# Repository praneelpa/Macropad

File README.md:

# Custom 6-Key Macropad for macOS

A compact 6-key macropad designed for macOS users, optimized for students. Features tap/hold combos for frequently used shortcuts like screenshots, clipboard, app switching, undo/redo, sleep, and quit.

---

## Images

### Overall Macropad
The overall part has a top case and a bottom case that fit together using screws (US 6# Screw).
It contains a PCB with the required components that sits on the bottom base, and the CherryMX keys stick out from the top base for access.

Made using Autodesk Fusion!

### Schematic
Made in KiCad!

### PCB
Made in KiCad!
Used the Cherry_MX_1.00u_PCB footprint from KiCad

---

## BOM (Bill of Materials)
Everything needed to make the macropad.
| Quantity | Part Description                | Notes |
|----------|--------------------------------|-------|
| 1        | XIAO RP2040 DIP                 | Microcontroller |
| 6        | Mechanical push buttons         | Tactile or mechanical switches |
| 1        | PCB                             | Custom designed in KiCAD |
| 1        | Case                            | 3D printed or custom enclosure |
| 1        | USB-C cable                     | For power and programming |
| 4       | Screws (6#)                     | To hold the top and bottom cases together|
| Misc     | Wires / solder / headers        | For connections |

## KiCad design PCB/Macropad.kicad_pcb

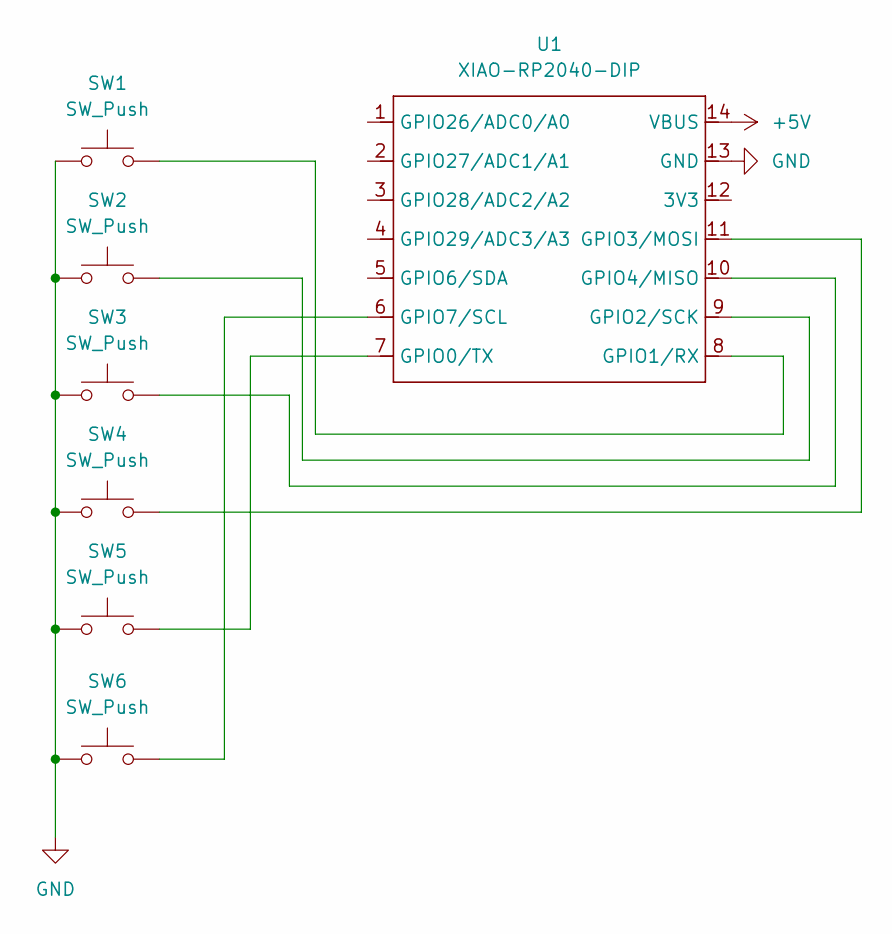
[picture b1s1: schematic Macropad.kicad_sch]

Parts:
SW1, SW2, SW3, SW4, SW5, SW6: SW_Push; SW_Cherry_MX_1.00u_PCB
U1: XIAO-RP2040-DIP

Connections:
+5V: U1.14 (VBUS)
GND: SW1.1, SW2.1, SW3.1, SW4.1, SW5.1, SW6.1, U1.13 (GND)
unnamed: SW5.2, U1.7 (GPIO0/TX)
unnamed: SW1.2, U1.8 (GPIO1/RX)
unnamed: SW2.2, U1.9 (GPIO2/SCK)
unnamed: SW4.2, U1.11 (GPIO3/MOSI)
unnamed: SW3.2, U1.10 (GPIO4/MISO)
unnamed: SW6.2, U1.6 (GPIO7/SCL)

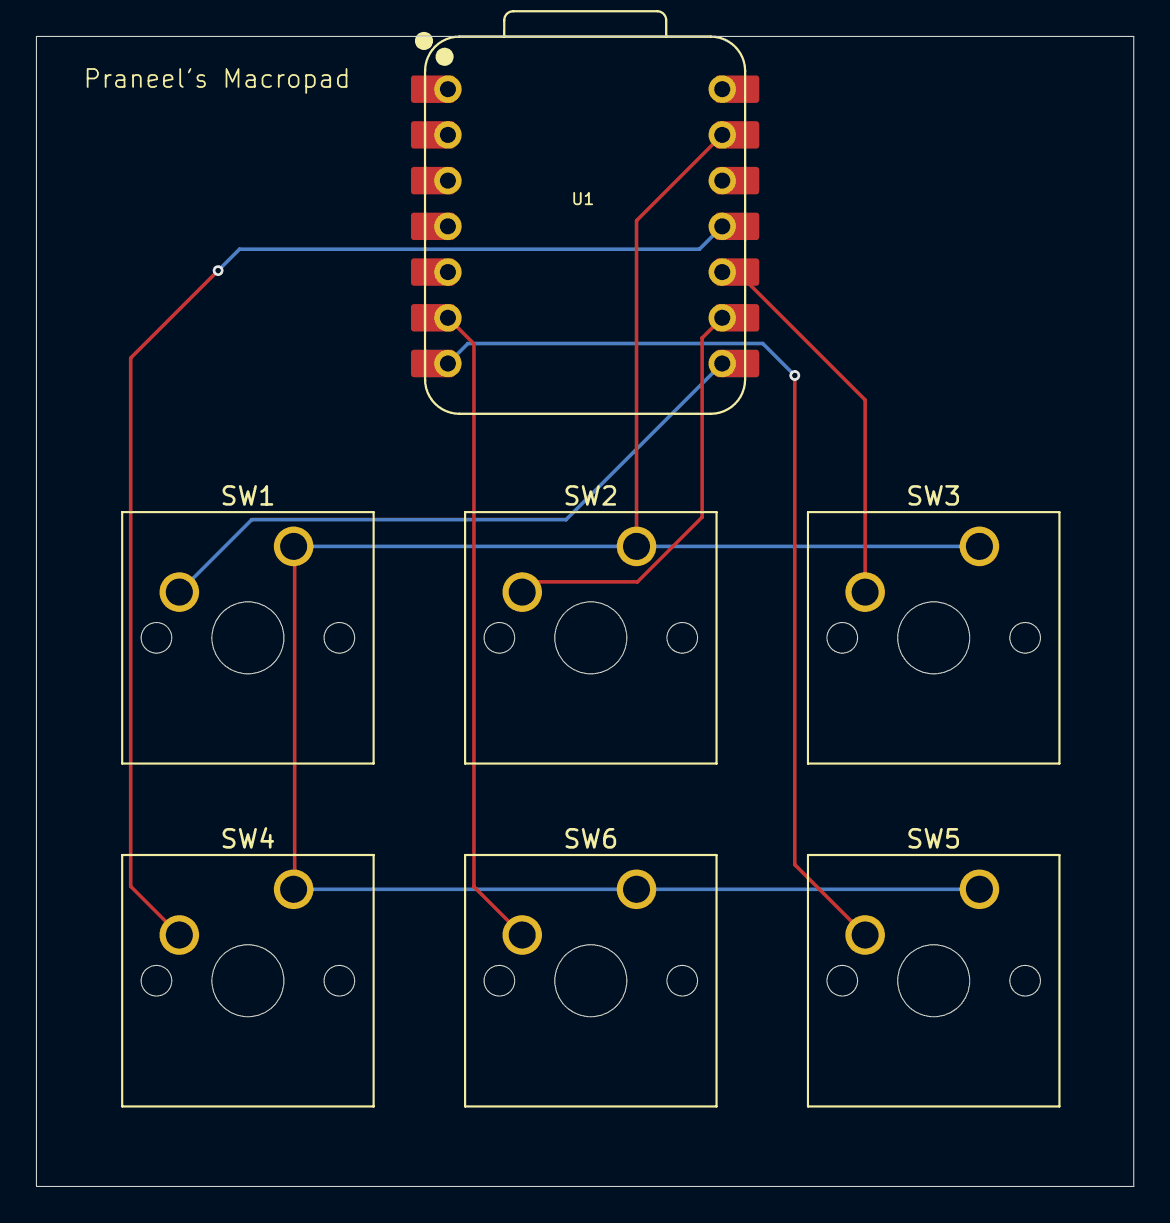
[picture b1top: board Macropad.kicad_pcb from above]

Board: 2 copper layers, 61.0 x 63.9 mm, 7 parts (0 on the bottom side), 7 nets.

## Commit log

2026-01-02 final
2026-02-03 pictures
